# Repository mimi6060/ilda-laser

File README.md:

# ilda-laser

A Rust workspace to control a laser projector like Pangolin's FB3/FB4 does
internally: stream ILDA points to a network laser DAC, or send DMX-512 over
Art-Net. Three crates:

- **`pc-client`** - CLI that runs on your PC/Mac. Plays `.ild` files, streams
  built-in test patterns, or sends DMX over Art-Net.
- **`pi-receiver`** - runs on a Raspberry Pi 3. Turns it into the actual
  laser DAC: receives the point stream over Ethernet and drives three
  MCP4922 SPI DAC chips to produce the analog X/Y/R/G/B signals the laser's
  ILDA input expects.
  **Abandoned**: replaced by a Laserworld ShowNET interface; kept for
  reference only.
- **`studio`** - Laser Studio, the live show controller for the Mac (see
  [Laser Studio](#laser-studio-studio)).

```
PC (pc-client)  --Ethernet, IDN protocol-->  Raspberry Pi 3 (pi-receiver)
                                                --SPI-->
                                    3x MCP4922 DAC chips (analog X/Y/R/G/B)
                                                --DB25 ILDA cable-->
                                               Laser
```

## Why you need this at all, not just an RJ45 cable

A PC's (or Pi's) network card only sends digital Ethernet frames. It cannot
put analog galvo-control voltages on a wire by itself. The laser's DB25 ILDA
input expects real analog X/Y/R/G/B signals, and Raspberry Pi GPIO pins are
digital 3.3V on/off - they can't drive that input directly either.

Some laser manuals include a "25 pin interface to Ethernet port" wiring
table (DB25 pin -> RJ45 pin, e.g. `X- -> Pin14`, `R -> Pin5`, ...). That is
**not** a network protocol - it's a trick to carry the same analog ILDA
signals over an Ethernet-style cable's wire pairs, purely to reach a longer
distance than a bulky ILDA cable allows. It is unrelated to what this
project does.

`pi-receiver` is the missing piece: an actual digital-to-analog converter,
built from a Pi plus three cheap SPI DAC chips, so the Pi can generate real
analog voltages on its own DB25 ILDA output.

## Protocol choice: IDN, not Ether Dream

`pc-client` and `pi-receiver` talk **IDN** (ILDA Digital Network) over UDP,
not Ether Dream. Both are supported by the underlying `laser-dac` crate, but
IDN was chosen for the Pi side because the crate ships a complete, tested
IDN server implementation (`laser_dac::receiver`) - `pi-receiver` just
implements the callback that receives points, instead of having to
hand-roll a DAC-side network protocol from scratch. `pc-client` still has
the `ether-dream` feature enabled too, in case you ever add a real
commercial Ether Dream DAC to the mix.

## Custom HAT board (order-ready-ish design)

`pi-receiver/hardware/DESIGN.md` has a full schematic-level design for a
Raspberry Pi HAT that does the 3x MCP4922 wiring below for you, on a board
that plugs straight onto the 40-pin header, with an onboard RJ45 jack wired
to the laser manual's exact pinout and adjustable-gain output stages (since
the laser's actual ILDA voltage range isn't documented anywhere). It
includes a full BOM with JLCPCB part numbers and a bring-up/trim procedure.
It is **not yet laid out as a PCB** - see that file's last section before
ordering anything.

## Hardware you need for `pi-receiver` (hand-wired version)

- A Raspberry Pi 3 (any variant with the 40-pin header), with Raspberry Pi
  OS and its Ethernet port on the same network as your PC.
- **Three MCP4922** dual-channel, 12-bit SPI DAC chips (~3-5€ each, widely
  available as breakout boards). Six analog channels total: X, Y, R, G, B,
  and one spare.
- Jumper wires, breadboard or perfboard, and eventually a DB25 connector to
  wire the DAC outputs into the laser's ILDA input pin-for-pin (X, Y, R, G,
  B, GND - see your laser's ILDA pinout, not the RJ45 wiring table).

### Wiring

| DAC | Bus / Chip Select | Channel A | Channel B |
|-----|--------------------|-----------|-----------|
| DAC1 | SPI0, CE0 (GPIO8) | X | Y |
| DAC2 | SPI0, CE1 (GPIO7) | R | G |
| DAC3 | SPI1, CE0 (GPIO18) | B | unused |

SPI0 is enabled by default on Raspberry Pi OS (`sudo raspi-config` ->
Interface Options -> SPI, if not). SPI1 needs one line added to
`/boot/firmware/config.txt`, then a reboot:

```
dtoverlay=spi1-1cs
```

Each MCP4922's `VDD`/`VREF` go to the Pi's 3.3V or 5V rail (check your DAC
breakout board's specs for which reference voltage it needs, and whether
that matches the voltage range your laser's ILDA input expects), `VSS` to
ground, `SCK`/`SDI`/`CS` to the matching SPI pins, and `VOUTA`/`VOUTB` to
the corresponding ILDA signal lines.

**Known limitation:** each DAC channel update is a separate SPI
transaction, so X and Y (and R/G, and B) update a few microseconds apart
rather than perfectly simultaneously. This is usually invisible at moderate
point rates; a shared hardware LDAC line across all three chips would
remove it entirely if it turns out to matter.

**Point-rate caveat:** Raspberry Pi OS is not a real-time OS, and each
laser point costs 5 blocking SPI syscalls here. Expect this to comfortably
handle test patterns and simple content, but not necessarily the full
20-30k points/second of a complex ILDA show without visible jitter. If that
turns out to be a problem in practice, the fix is offloading the
time-critical DAC clocking to a microcontroller (e.g. a Raspberry Pi Pico
using its PIO peripheral) that the Pi feeds over UART - not implemented
here.

## Safety

You're building a hobby laser DAC. Before pointing it at anything:
- Start with `pc-client pattern cross` at a low `--pps` (e.g. 2000) and
  verify X/Y orientation and center point are correct.
- Make sure your laser's safety interlock / scanner-fail protection is
  functional, so a frozen or garbage point stream doesn't leave the beam
  stuck on and bright at one spot.
- Never point a laser at eyes; keep the beam below eye level or in a
  controlled/enclosed setup while testing.

## Building and running (via Docker - no local Rust install needed on the PC/Mac)

```sh
# Build both crates
docker run --rm -v "$PWD":/app -w /app -v ilda-laser-cargo:/usr/local/cargo/registry \
  -v ilda-laser-target:/app/target rust:1-bookworm cargo build --workspace --release

# pc-client: discover DACs on the network (needs host networking for UDP)
docker run --rm --network host -v "$PWD":/app -w /app -v ilda-laser-cargo:/usr/local/cargo/registry \
  -v ilda-laser-target:/app/target rust:1-bookworm ./target/release/ilda-laser discover

# pc-client: test pattern
docker run --rm --network host -v "$PWD":/app -w /app -v ilda-laser-cargo:/usr/local/cargo/registry \
  -v ilda-laser-target:/app/target rust:1-bookworm ./target/release/ilda-laser pattern cross

# pc-client: play an ILDA file
docker run --rm --network host -v "$PWD":/app -w /app -v ilda-laser-cargo:/usr/local/cargo/registry \
  -v ilda-laser-target:/app/target rust:1-bookworm ./target/release/ilda-laser play ./show.ild

# pc-client: DMX over Art-Net (if your laser/gateway speaks it)
docker run --rm --network host -v "$PWD":/app -w /app -v ilda-laser-cargo:/usr/local/cargo/registry \
  -v ilda-laser-target:/app/target rust:1-bookworm \
  ./target/release/ilda-laser dmx 192.168.1.50 --channels 255,0,0,0,0,0,0,0,0,0,0,0,0,0,0,0,0,0
```

`--network host` is required for anything that talks to the network (IDN
discovery/streaming, Art-Net) because Docker Desktop's default bridge
network does not forward UDP broadcast/multicast to your LAN.

### `pi-receiver`: build and run directly on the Raspberry Pi

Cross-compiling `rppal` (it needs Linux `/dev/spidev` access) is more
hassle than it's worth for a one-off. Simplest path: install Rust directly
on the Pi and build there.

```sh
# On the Pi:
curl https://sh.rustup.rs -sSf | sh -s -- -y
source "$HOME/.cargo/env"

git clone <this repo's URL> ilda-laser
cd ilda-laser
cargo build --release -p pi-receiver

# Enable SPI0 (raspi-config -> Interface Options -> SPI) and add
# `dtoverlay=spi1-1cs` to /boot/firmware/config.txt, then reboot.

sudo ./target/release/pi-receiver pi-laser
# (sudo, or add your user to the `spi`/`gpio` groups, so it can open
# /dev/spidev*)
```

It prints the IDN service name and address it's listening on. From the PC:

```sh
./target/release/ilda-laser discover      # should list idn:pi-laser
./target/release/ilda-laser pattern cross --device idn:pi-laser
```

## Web control panel

`pi-receiver` also starts a small web server on port 8080 - no app or PC
CLI needed. From any phone or computer on the same WiFi as the Pi, open
`http://<pi's IP address>:8080/`. It talks to the same DAC output as the
IDN receiver above, so the two share a "last one to send something wins"
relationship - don't expect them to usefully run at the same time.

Find the Pi's IP address with `hostname -I` run on the Pi itself, or check
your router's connected-devices list.

Four tabs:

- **Pattern** - built-in shapes (circle, square, triangle, cross, line,
  star, spiral, dot grid), with a live canvas preview that updates as you
  adjust color/size/speed, before anything is sent to the laser.
- **Text** - type text, it's rendered with a built-in single-stroke vector
  font (A-Z, 0-9, space, `. , ! ' -`) - not a real typeface, but
  laser-drawable and self-contained.
- **Scenes** - save the current pattern/text as a named scene with its own
  duration, then either play one on demand or start a playlist that
  auto-advances through all saved scenes on a timer (the same idea as the
  original laser's own "Scene management", reimplemented so the Pi doesn't
  need that app). Manual Apply/Play always interrupts the playlist.
- **Calibration** - offset/scale/rotation applied to *every* point
  regardless of source (this panel or the IDN network feed) - the hardware
  equivalent of a projector's position/size/keystone adjustment. Saved to
  disk, so it survives a restart.

`pi-receiver` takes an optional second argument for where scenes and
calibration get saved (defaults to the current directory):
`pi-receiver pi-laser /home/pi/laser-data`.

## Laser Studio (`studio`)

A live laser show controller for the Mac: generated shapes, laser text,
abstracts and effects in a cue grid with four layers, chasers, a timeline,
live modifiers and LFOs, safety zones and projector calibration. Looks are
our own procedural content; `.ild` files you have the rights to can be
imported at runtime. The UI is a local web page (French text).

```sh
cargo run --release -p laser-studio                          # preview only
cargo run --release -p laser-studio -- --help                # every option
cargo run --release -p laser-studio -- --port 8090 --data-dir /tmp/studio-test
```

Then open http://127.0.0.1:8080/ (`--port` to change). The UI is bound to
localhost only, since it can switch a laser on. Scenes, cues, calibration
and settings are saved in `studio-data/` (`--data-dir` to change).
`studio/packaging/macos/build_app.sh` builds a `Laser Studio.app` that
starts with `--app` (data in `~/Library/Application Support/Laser Studio`,
a free port from 8080 up, the page opens in the browser).

### Arming, emergency stop and the hardware stop

- The laser **always starts disarmed**, whatever the output. Only the
  operator arms it: the button at the top right, or Space. Losing or
  changing the output disarms it again.
- **Escape is a latching emergency stop**: the output goes dark at once and
  the laser cannot be armed again until the operator presses
  *Réinitialiser l'arrêt d'urgence*. Shift+Escape is a plain disarm.
- On disarm, emergency stop, blackout and shutdown the studio keeps sending
  dark (or empty) frames rather than going silent.
- Nothing received from the network or a controller (OSC, Art-Net, sACN,
  timecode) can arm the laser; blackout and the emergency stop are always
  accepted.

**Hardware stop.** These are software stops. They depend on the Mac, the
studio, the network and the receiving device all working, and they are
**never sufficient on their own**. The real stop is hardware: the
projector's interlock, an emergency-stop button that cuts the laser, and
its key switch. Wire and test them before any show, keep the E-stop within
the operator's reach, and never assume a DAC, MadMapper or the ShowNET
blanks by itself when the network drops or the studio stops sending: what
these devices do then is not guaranteed.

### Outputs

The output is chosen in *Réglages › Sorties et projecteurs* (remembered
between runs) or for one run on the command line. Every output honours
arm / disarm, the emergency stop and blackout, after calibration and the
safety stage (zones, power caps, strobe limiter, static beam guard).

- **Preview** (default): nothing leaves the Mac. The preview shows the exact
  frame that would be sent, with its point count and frame rate; keep that
  above ~15 frames/s or the image flickers.
- **PONK to MadMapper / MadLaser** (`--ponk`, or `--ponk HOST:PORT`; alone it
  targets MadMapper on this Mac). MadMapper, with its own Laserworld
  licence, drives the ShowNET. MadMapper keeps showing the last frame it
  received, so the studio never stops sending: while disarmed every tick is
  an empty frame.
- **Open DACs** (`--device <id>` or `--device auto`): Helios (USB),
  HeliosPRO (IDN over Ethernet) and Ether Dream (Ethernet), on the
  projector's ILDA input in place of the ShowNET. Details below.
- **ShowNET SD card + Art-Net**: *Réglages › Carte SD ShowNET* exports a
  bank of our cues as `001.ild`–`229.ild` (`000` and `230`–`255` are left
  alone), with calibration, zones and power caps baked into every file.
  With `--shownet-artnet IP[:PORT]` the studio then picks the file to play
  and the intensity over Art-Net; disarmed means intensity 0 and pattern 0.
  The box plays those files without the studio, so its hardware stop is the
  only real stop.
- **Native ShowNET**: not available. Its streaming protocol is encrypted;
  native output waits for Laserworld's official API, which has been
  requested. Until then use PONK, an open DAC or the SD card.

Use wired Ethernet for any network output; Wi-Fi is not a safe link for a
laser.

### Open DACs (Helios, HeliosPRO, Ether Dream)

The ShowNET reaches the lasers through an ILDA DB25 cable; any ILDA DAC can
take its place on that cable, with nothing changed on the lasers:

- **Helios** (USB): plug it into the Mac, no driver needed. libusb is
  built from source into the studio (`libusb1-sys` `vendored`), so there
  is nothing to install with Homebrew; a C compiler (Xcode command line
  tools) is enough to build.
- **HeliosPRO** (IDN over Ethernet) and **Ether Dream** (Ethernet): on the
  same network as the Mac.

```sh
cargo run --release -p laser-studio -- --list-devices            # scan, print the ids, exit
cargo run --release -p laser-studio -- --device helios:<name>    # drive that DAC
cargo run --release -p laser-studio -- --device auto --pps 30000 # first DAC found
```

The same list is in *Réglages › Sorties et projecteurs* (*Rechercher*),
where a DAC can be chosen and reconnected without a restart. Scanning only
happens when asked and is read-only: it never connects, arms or sends a
frame. While the studio drives a DAC, a rescan leaves USB out so the
running Helios is never touched.

Points per second: `--pps` (default: the value saved with the output, else
30 000; Helios accepts 7 to 65 535). A Helios USB frame holds at most 4095
points: a bigger frame is thinned evenly before it is sent, and a thinned
point goes dark wherever a blanked travel was skipped, so thinning never
draws a lit jump. Keep the point budget under 4000 for the full detail.

### Audio, controllers and show control

- **Audio**: analysed natively (tempo, beats, onsets, spectrum), from the
  Mac's microphone or any audio input (`--audio-device <name>`,
  `--no-audio` for none), from a song played by the studio, or from what
  the Mac itself plays (*Son du Mac*: Cargo feature `system-audio`,
  macOS 14.6+; otherwise route it through a loopback device such as
  BlackHole).
- **MIDI**: controllers over CoreMIDI, with MIDI learn and LED feedback
  (`--no-midi` opens no port). `--list-controls` prints every control id.
- **OSC**: `/ls/…` addresses onto the same control ids (`--osc`, or
  `--osc IP:PORT`; alone 127.0.0.1:8000).
- **Art-Net in**: DMX from a lighting console (`--artnet`, or
  `--artnet IP:PORT`; alone 127.0.0.1:6454).
- **sACN in** (E1.31): the same DMX control, enabled in *Réglages*.
- **Timecode in**: MIDI Time Code, LTC on an audio channel or Art-Net
  timecode drives the timeline only, once the operator arms TC-IN.

All network inputs pass through one gate in *Entrées externes*, and none of
them can arm the laser.

### Ableton Link (optional, GPL, off by default)

The tempo can follow an Ableton Link session (tempo and phase) with the
Cargo feature `ableton-link`. It compiles Ableton's Link library, which
is licensed GPLv2+, so it is **not** in a default build (no GPL code there:
check with `cargo tree -p laser-studio`), and *Réglages › Ableton Link*
stays greyed. A binary built with the feature is a GPL combined work: keep
it for your own use, do not distribute it. It can't be combined with the
`shownet` feature: the build refuses.

```sh
# needs CMake (and Xcode's command line tools, for libclang)
cargo run --release -p laser-studio --features ableton-link
```

Link is off at every start; once turned on it discovers peers by multicast
on the local network. It only moves the tempo: it never arms the laser.
Only the operator's tempo controls (BPM field, Tap, ×2, ÷2, and the same
controls from MIDI, OSC or the keyboard) propose a tempo to the session;
opening a project, a macro or a show list never changes the session's
tempo. `--all-features` fails to build on purpose (`ableton-link` and
`shownet` exclude each other).

### Building and testing

```sh
cargo build -p laser-studio
cargo test -p laser-studio
cargo clippy -p laser-studio --all-targets -- -D warnings
npm --prefix studio/e2e test        # Playwright UI tests, preview only
```

Tests run in preview only, on a temporary data directory: they never open a
real output.

## Usage (`pc-client`)

```
ilda-laser discover
ilda-laser play <file.ild> [--device <id>] [--pps 30000] [--fps 25]
ilda-laser pattern <circle|square|triangle|cross> [--device <id>] [--pps 30000] [--scale 0.8] [--color 255,0,0]
ilda-laser dmx <ip[:port]> --universe 0 --channels 255,0,0,... [--repeat-ms 1000]
```

Run with `RUST_LOG=debug` for verbose logging from the underlying
`laser-dac` crate when diagnosing a connection problem, on either side.

## Coordinate system

Points use normalized coordinates: X -1.0 (left) to 1.0 (right), Y -1.0
(bottom) to 1.0 (top). Colors are 0-65535 in `pc-client`'s internal
representation (0.0-1.0 once received by `pi-receiver`); the CLI's
`--color` flag takes 0-255 per channel and scales it up.

## Status / testing

Everything here has been built, unit-tested (`cargo test --workspace`) and
clippy-clean without physical hardware - the coordinate/color/DAC-word
conversion math and DMX packet encoding are covered by tests, but the
actual IDN network exchange and SPI/DAC output have not been verified
against a real Pi + DAC chips + laser. Go slowly, verify wiring and
orientation with `pattern cross` at a low point rate first, and check the
DAC's analog output with a multimeter/scope before trusting it near a real
laser diode driver.

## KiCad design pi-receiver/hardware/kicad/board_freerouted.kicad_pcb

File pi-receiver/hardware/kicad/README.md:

# Pi Laser HAT - KiCad files

Generated from `../DESIGN.md`'s schematic-level spec via KiCad 8's
`pcbnew` Python API (placement + netlist) and Freerouting 2.4.1 (routing),
both run inside Docker - no local KiCad or Java install needed to
regenerate these. **Status: DRC-clean, gerbers exported, ready for
review before ordering.**

## Files

| File | What it is |
|------|------------|
| `board.kicad_pcb` (+ `.kicad_pro`/`.kicad_prl`) | All 40 parts placed, every net assigned, **not routed** (ratsnest only). DRC-clean for placement: zero shorts, zero courtyard overlaps, zero parts outside the outline. |
| `board_freerouted.kicad_pcb` (+ `.kicad_pro`) | **The final routed board.** DRC-clean: 0 errors, 7 warnings (all cosmetic silkscreen-text clipping, e.g. a reference designator slightly overlapping a pad's solder mask - doesn't affect fabrication or function). This is the file the gerbers below were exported from. |
| `build_board.py` | Places every component and wires every net from `DESIGN.md`, computed from each footprint's real (measured, not guessed) courtyard geometry. Produces `board.kicad_pcb`. |
| `export_dsn.py` | Exports `board.kicad_pcb` as Specctra DSN (`board.dsn`) for Freerouting, and widens the default trace width/clearance from KiCad's 0.2mm default to 0.25mm (this board has plenty of room; no reason to push fab tolerances). |
| `import_ses.py` | Imports Freerouting's routed session (`board_routed.ses`) back onto `board.kicad_pcb`, saving `board_freerouted.kicad_pcb`. |
| `board_placed.pos` | Component placement (CPL) file exported from the placement-only board - superseded by `../gerbers/board_freerouted-CPL.csv`, kept for reference. |
| `placement_drc.json`, `freerouted_drc.json` | Full DRC reports (`kicad-cli pcb drc --format json`) for the placement-only and final routed boards. |
| `placement_render.png`, `board_freerouted.png` | Top-view renders (SVG via `kicad-cli`, rasterized with `rsvg-convert`). |

`../gerbers/` has the fabrication output: Gerbers, drill files, CPL, and a
BOM, ready to hand to JLCPCB (or any fab). See that directory's own notes
below.

## How the routing was actually done

The first attempt (now removed) was a hand-written naive Manhattan router
- it achieved full connectivity but left 417 DRC violations (mostly
clearance/crossings) because it didn't do real clearance checking, just
avoided literal trace-to-trace intersections. That wasn't good enough to
order against.

This version uses **Freerouting** (github.com/freerouting/freerouting), a
real autorouter built for exactly this, via the standard KiCad workflow:

1. `export_dsn.py`: `board.kicad_pcb` -> Specctra DSN (`board.dsn`), with
   trace width/clearance widened to 0.25mm.
2. Freerouting run headless (needs Java 25 - the released jar is compiled
   for a newer class file version than Java 21/23 support; a Java 21 or 23
   JRE fails with `UnsupportedClassVersionError`):
   ```
   java -Djava.awt.headless=true -jar freerouting.jar \
     -de board.dsn -do board_routed.ses -mp 20
   ```
   Completed in ~7 seconds: fanout, then 6 auto-routing passes, finishing
   with **0 unrouted, 0 violations**, score 999.99/1000.
3. `import_ses.py`: the resulting `.ses` imported back onto
   `board.kicad_pcb`, saved as `board_freerouted.kicad_pcb`.
4. `kicad-cli pcb drc` on the result: **0 errors, 7 warnings** (cosmetic
   silkscreen only - see `freerouted_drc.json` for exact details).

The `freerouting.jar` itself (64MB) isn't committed here - re-download
from the GitHub releases page (v2.4.1) to reproduce.

## What's actually verified

- **Board outline and mounting holes**: cross-checked against both the
  official `hat-board-mechanical.pdf` (raspberrypi/hats repo) and the
  official KiCad team's own `raspberrypi_hat` template project - both
  agree exactly (65x56mm, 3mm corners, holes at (3.5,3.5)/(61.5,3.5)/
  (3.5,52.5)/(61.5,52.5)).
- **GPIO header placement**: reused the exact same footprint, relative
  position, rotation, and layer as the official KiCad template.
- **MCP4922 and MCP6004 pinouts**: read directly from Microchip's real
  datasheets (DS22250A and DS20001733L). This caught two things
  `DESIGN.md`'s original text missed: the MCP4922 has a hardware
  `/SHDN` pin (9) separate from the per-channel SHDN bit in the SPI
  command word, and two separate VREFA/VREFB pins, not one shared VREF -
  both now wired correctly; see `DESIGN.md`'s note.
- **Placement**: zero courtyard overlaps, zero shorted pads, zero parts
  outside the board outline.
- **Routing**: 0 DRC errors after Freerouting + KiCad DRC, as above.

## What's not verified

- **RJ45 footprint**: standard-library `RJ45_Amphenol_54602-x08_Horizontal`
  used as a stand-in for the actual BOM part (EVERCOM 5301-8P8C) - both
  are generic unshielded right-angle THT 8P8C jacks, but their exact pin
  spacing/mounting-peg positions were not cross-checked against the real
  5301-8P8C datasheet. **Check this specifically before ordering** - if it
  doesn't match, only J1's footprint needs to change.
- **Nothing here has touched real hardware.** Placement, pinouts, and
  routing are verified against primary sources and DRC; the actual analog
  design (gain values, differential mirror topology) is still the
  unbench-tested design from `DESIGN.md` - follow its bring-up/trim
  procedure once assembled.
- The 7 remaining cosmetic silkscreen warnings weren't chased to zero
  (diminishing returns - they don't affect fabrication).

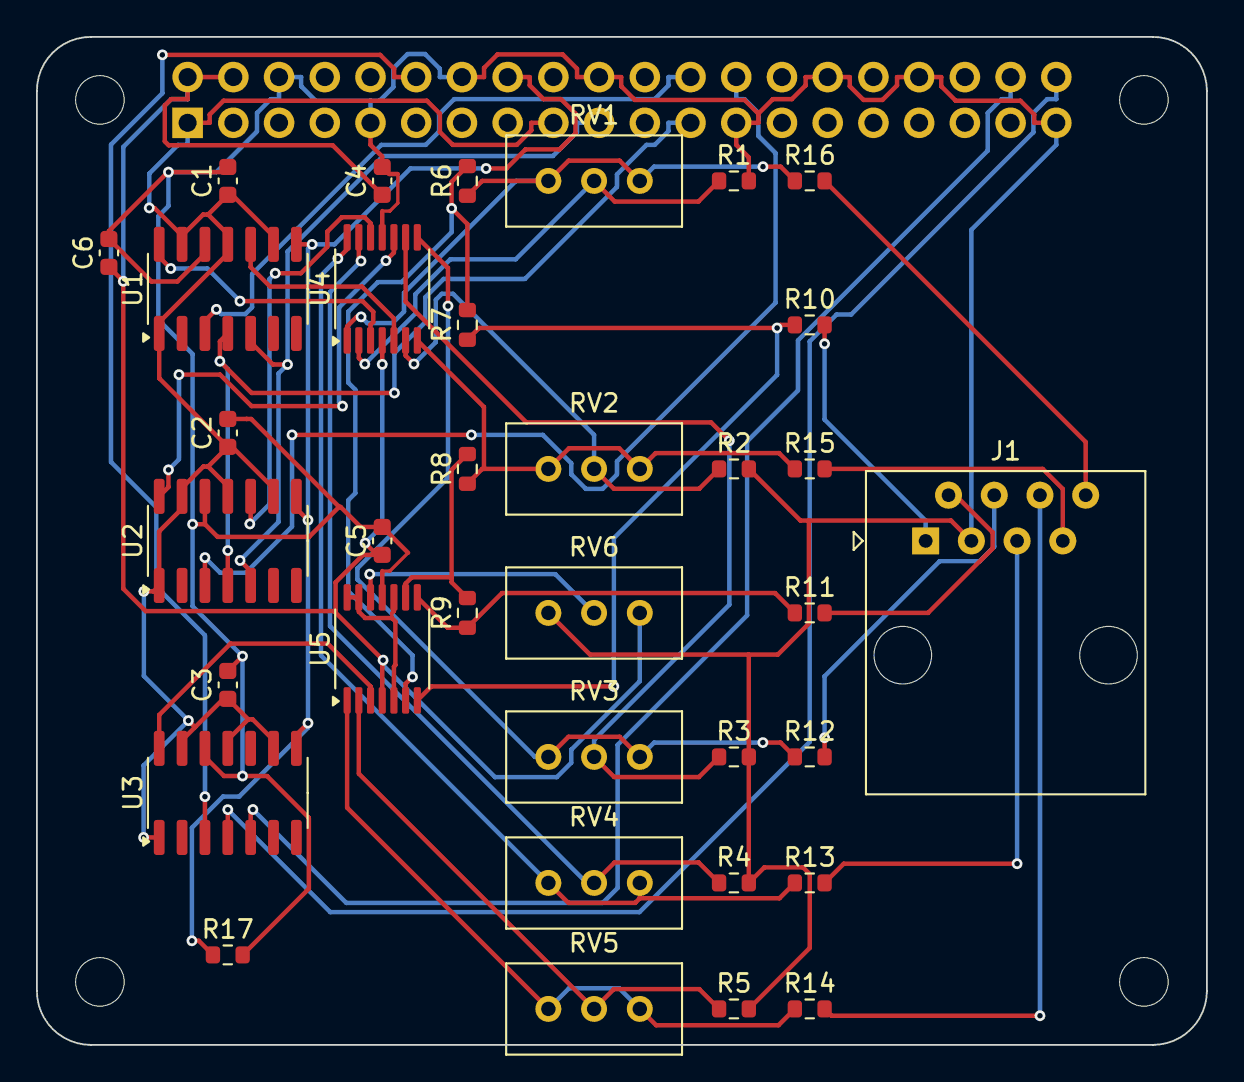
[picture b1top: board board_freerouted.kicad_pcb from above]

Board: 2 copper layers, 65.0 x 56.0 mm, 40 parts (1 on the bottom side), 39 nets.

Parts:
C1, C2, C3, C4, C5: 100nF; C_0603_1608Metric
C6: 10uF; C_0603_1608Metric
H1, H2, H3, H4: MountingHole_2.7mm_M2.5
J1: RJ45_Amphenol_54602-x08_Horizontal
J2: PinSocket_2x20_P2.54mm_Vertical
R1, R2, R3, R4, R5, R6, R7, R8, R9: 20k 1%; R_0603_1608Metric
R10, R11, R12, R13, R14, R15, R16: 470; R_0603_1608Metric
R17: 10k; R_0603_1608Metric
RV1, RV2, RV3, RV4, RV5, RV6: 10k; Potentiometer_Bourns_3296W_Vertical
U1, U2, U3: MCP4922-E/SL; SOIC-14_3.9x8.7mm_P1.27mm
U4, U5: MCP6004-I/ST; TSSOP-14_4.4x5mm_P0.65mm

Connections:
B_FB: R5.1, RV5.2, U5.2
DAC_B: U3.14, U5.3
DAC_G: U2.10, U4.12
DAC_R: U2.14, U4.10
DAC_X: U1.14, U4.3
DAC_Y: U1.10, U4.5
GND: C1.2, C2.2, C3.2, C4.2, C5.2, C6.2, J1.3, J2.6, J2.9, J2.14, J2.20, J2.25, J2.30, J2.34, J2.39, R1.2, R2.2, R3.2, R4.2, R5.2, R17.2, RV6.3, U1.12, U2.12, U3.12, U4.11, U5.11
G_FB: R4.1, RV4.2, U4.13
LDAC: J2.16, R17.1, U1.8, U2.8, U3.8
RJ_B: J1.6, R14.2
RJ_G: J1.5, R13.2
RJ_R: J1.4, R12.2
RJ_X_MINUS: J1.1, R10.2
RJ_X_PLUS: J1.8, R16.2
RJ_Y_MINUS: J1.2, R11.2
RJ_Y_PLUS: J1.7, R15.2
R_FB: R3.1, RV3.2, U4.9
SIG_B: R14.1, RV5.1, RV5.3, U5.1
SIG_G: R13.1, RV4.1, RV4.3, U4.14
SIG_R: R12.1, RV3.1, RV3.3, U4.8
SPI0_CE0: J2.24, U1.3
SPI0_CE1: J2.26, U2.3
SPI0_SCK: J2.23, U1.4, U2.4
SPI0_SDI: J2.19, U1.5, U2.5
SPI1_CE0: J2.12, U3.3
SPI1_SCK: J2.40, U3.4
SPI1_SDI: J2.38, U3.5
VBIAS: U5.5, U5.10, U5.13, U5.14
VBIAS_REF: RV6.2, U5.12
VDD_3V3: C1.1, C2.1, C3.1, J2.1, J2.17, U1.1, U1.9, U1.11, U1.13, U2.1, U2.9, U2.11, U2.13, U3.1, U3.9, U3.11, U3.13
VDD_5V: C4.1, C5.1, C6.1, J2.2, J2.4, RV6.1, U4.4, U5.4
X_MINUS: R7.1, R10.1, U5.7
X_MIRROR_FB: R6.2, R7.2, U5.6
X_PLUS: R6.1, R16.1, RV1.1, RV1.3, U4.1
X_PLUS_FB: R1.1, RV1.2, U4.2
Y_MINUS: R9.1, R11.1, U5.8
Y_MIRROR_FB: R8.2, R9.2, U5.9
Y_PLUS: R8.1, R15.1, RV2.1, RV2.3, U4.7
Y_PLUS_FB: R2.1, RV2.2, U4.6

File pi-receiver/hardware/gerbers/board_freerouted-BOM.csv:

Comment,Designator,Footprint,LCSC Part #
MCP4922-E/SL,"U1,U2,U3",SOIC-14_3.9x8.7mm_P1.27mm,C39851
MCP6004-I/ST,"U4,U5",TSSOP-14_4.4x5mm_P0.65mm,C185811
RJ45 8P8C right-angle unshielded,J1,RJ45_Amphenol_54602-x08_Horizontal,C3097717
10k trimmer potentiometer,"RV1,RV2,RV3,RV4,RV5,RV6",Potentiometer_Bourns_3296W_Vertical,
20k 1%,"R1,R2,R3,R4,R5,R6,R7,R8,R9",R_0603_1608Metric,
470R,"R10,R11,R12,R13,R14,R15,R16",R_0603_1608Metric,
10k,R17,R_0603_1608Metric,
100nF,"C1,C2,C3,C4,C5",C_0603_1608Metric,
10uF,C6,C_0603_1608Metric,
2x20 female header 2.54mm (stacking/tall THT - source separately, hand-solder),J2,PinSocket_2x20_P2.54mm_Vertical,

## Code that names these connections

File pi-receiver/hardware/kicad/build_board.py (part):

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RJ_FP = ("Connector_RJ", "RJ45_Amphenol_54602-x08_Horizontal")
x_rj = next_column(*RJ_FP, 0)
rj = place(*RJ_FP, "J1", x_rj, 28, rot=0)
rj_pin_nets = {1: "RJ_X_MINUS", 2: "RJ_Y_MINUS", 3: "GND", 4: "RJ_R",
               5: "RJ_G", 6: "RJ_B", 7: "RJ_Y_PLUS", 8: "RJ_X_PLUS"}
for pin, netname in rj_pin_nets.items():
    wire(rj, pin, netname)
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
